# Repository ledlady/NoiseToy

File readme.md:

# NoiseToy
NoiseToy is a raspberry pi powered effect pedal.
Project files will follow soon.

This Project is inspired by and is based on the Pedal-Pi Project by Electrosmash: https://www.electrosmash.com/pedal-pi
Software followes mpi3d: https://github.com/mpi3d/pedal-pi

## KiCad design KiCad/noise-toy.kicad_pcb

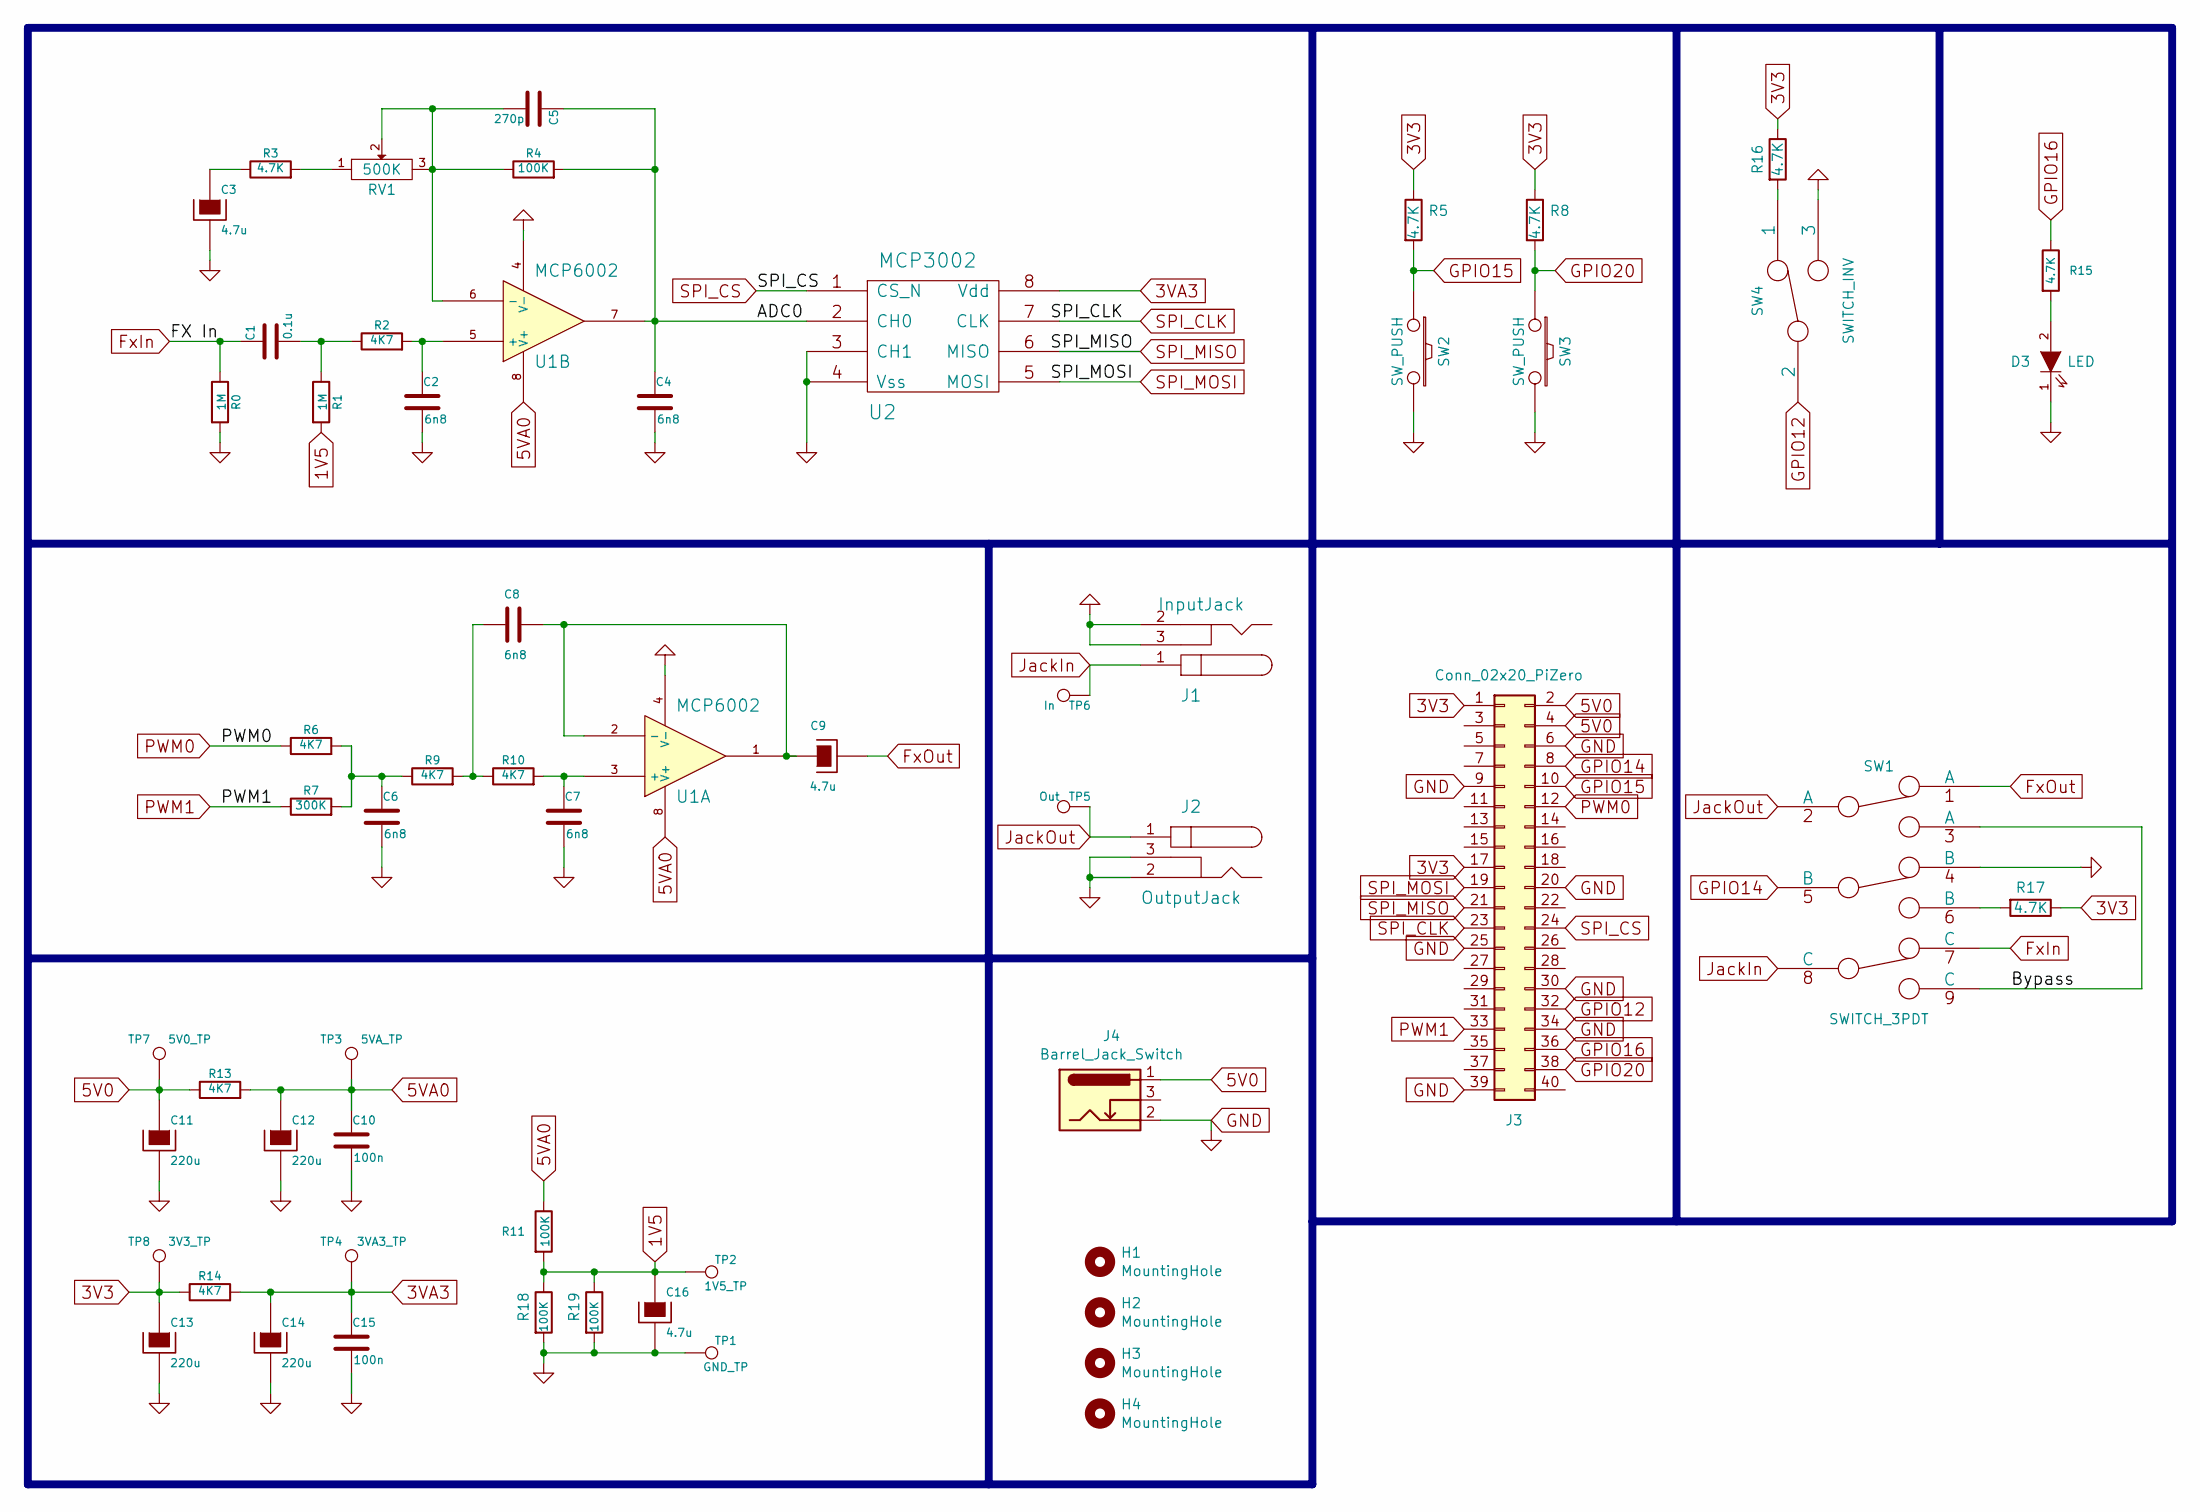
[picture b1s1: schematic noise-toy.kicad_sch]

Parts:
C1: 0.1u; C_Rect_L4.0mm_W2.5mm_P2.50mm
C2, C4, C6, C7, C8: 6n8; C_Rect_L4.0mm_W2.5mm_P2.50mm
C3, C9, C16: 4.7u; CP_Radial_D5.0mm_P2.00mm
C5: 270p; C_Rect_L4.0mm_W2.5mm_P2.50mm
C10, C15: 100n; C_Rect_L7.0mm_W2.5mm_P5.00mm
C11, C12, C13, C14: 220u; CP_Radial_D6.3mm_P2.50mm
D3: LED; LED_D5.0mm
H1, H2, H3, H4: MountingHole; MountingHole_3.2mm_M3
J1: InputJack; Audio_TRS_635_Stereo
J2: OutputJack; Audio_TRS_635_Stereo
J3: Conn_02x20_PiZero; PinHeader_2x20_P2.54mm_Vertical
J4: Barrel_Jack_Switch; BarrelJack_Horizontal
R0, R1: 1M; R_Axial_DIN0207_L6.3mm_D2.5mm_P10.16mm_Horizontal
R2, R6, R9, R10, R13, R14: 4K7; R_Axial_DIN0207_L6.3mm_D2.5mm_P10.16mm_Horizontal
R3, R5, R8, R15, R16, R17: 4.7K; R_Axial_DIN0207_L6.3mm_D2.5mm_P10.16mm_Horizontal
R4, R11, R18, R19: 100K; R_Axial_DIN0207_L6.3mm_D2.5mm_P10.16mm_Horizontal
R7: 300K; R_Axial_DIN0207_L6.3mm_D2.5mm_P10.16mm_Horizontal
RV1: 500K; Amphenol_N6S25T0C
SW1: SWITCH_3PDT; Switch_3PDT
SW2, SW3: SW_PUSH; Button_SPST
SW4: SWITCH_INV; Switch_SPDT
TP1: GND_TP; TestPoint_Pad_D2.5mm
TP2: 1V5_TP; TestPoint_Pad_D2.5mm
TP3: 5VA_TP; TestPoint_Pad_D2.5mm
TP4: 3VA3_TP; TestPoint_Pad_D2.5mm
TP5: Out; TestPoint_Pad_D2.5mm
TP6: In; TestPoint_Pad_D2.5mm
TP7: 5V0_TP; TestPoint_Pad_D2.5mm
TP8: 3V3_TP; TestPoint_Pad_D2.5mm
U1: MCP6002; DIP-8_W7.62mm_Socket_LongPads
U2: MCP3002; DIP-8_W7.62mm_Socket_LongPads

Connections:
1V5: C16.1, R1.2, R11.2, R18.1, R19.1, TP2.1
3V3: C13.1, J3.1, J3.17, R5.1, R8.1, R14.1, R16.1, R17.1, TP8.1
3VA3: C14.1, C15.1, R14.2, TP4.1, U2.8 (Vdd)
5V0: C11.1, J3.2, J3.4, J4.1, R13.1, TP7.1
5VA0: C10.1, C12.1, R11.1, R13.2, TP3.1, U1.8 (V+)
/ADC0: C4.1, C5.1, R4.2, U1.7, U2.2 (CH0)
/Bypass: SW1.3 (A), SW1.9 (C)
FxIn: C1.1, R0.1, SW1.7 (C)
FxOut: C9.2, SW1.1 (A)
GND: C2.2, C3.2, C4.2, C6.2, C7.2, C10.2, C11.2, C12.2, C13.2, C14.2, C15.2, C16.2, D3.1 (K), J1.2, J1.3, J2.2, J2.3, J3.6, J3.9, J3.20, J3.25, J3.30, J3.34, J3.39, J4.2, R0.2, R18.2, R19.2, SW1.4 (B), SW2.2, SW3.2, SW4.3, TP1.1, U1.4 (V-), U2.3 (CH1), U2.4 (Vss)
GPIO12: J3.32, SW4.2
GPIO14: J3.8, SW1.5 (B)
GPIO15: J3.10, R5.2, SW2.1
GPIO16: J3.36, R15.1
GPIO20: J3.38, R8.2, SW3.1
JackIn: J1.1, SW1.8 (C), TP6.1
JackOut: J2.1, SW1.2 (A), TP5.1
unnamed: C1.2, R1.1, R2.1
unnamed: C2.1, R2.2, U1.5 (+)
unnamed: C3.1, R3.1
unnamed: C5.2, R4.1, RV1.2, RV1.3, U1.6 (-)
unnamed: C6.1, R6.2, R7.2, R9.1
unnamed: C7.1, R10.2, U1.3 (+)
unnamed: C8.1, C9.1, U1.1, U1.2 (-)
unnamed: C8.2, R9.2, R10.1
unnamed: D3.2 (A), R15.2
unnamed: R3.2, RV1.1
unnamed: R16.2, SW4.1
unnamed: R17.2, SW1.6 (B)
PWM0: J3.12, R6.1
PWM1: J3.33, R7.1
SPI_CLK: J3.23, U2.7 (CLK)
SPI_CS: J3.24, U2.1 (CS_N)
SPI_MISO: J3.21, U2.6 (MISO)
SPI_MOSI: J3.19, U2.5 (MOSI)

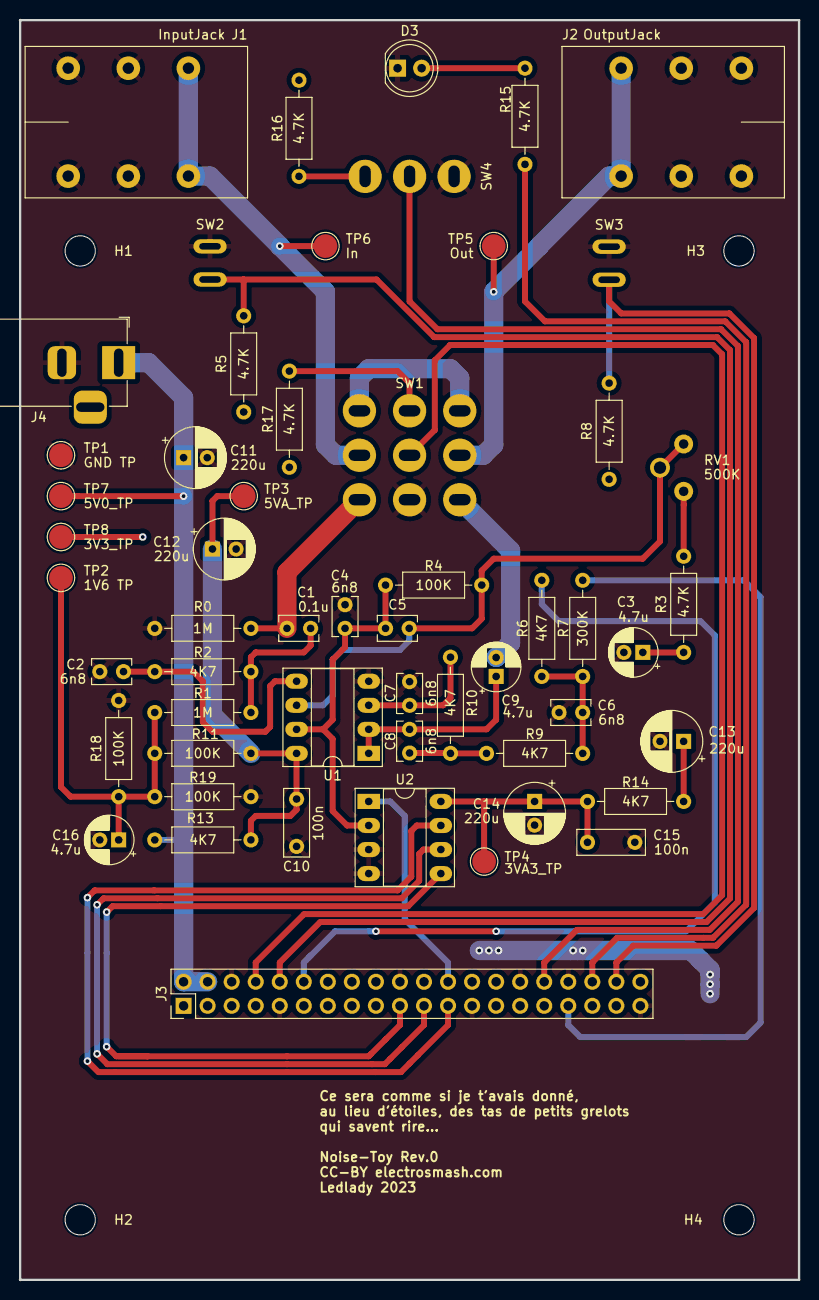
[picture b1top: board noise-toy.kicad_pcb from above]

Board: 2 copper layers, 82.3 x 133.1 mm, 59 parts (0 on the bottom side), 35 nets.

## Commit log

2023-09-11 Added KiCad7 design files
2023-09-11 Fixed wrong hole size in TRS jack Moved footprints to noise-toy.pretty
2023-09-11 Changed position of TRS jack
2023-09-11 Changed pcb attribution
2023-09-11 Added schematic and documentation notes
2023-09-11 Added jlcpcb gerber files to production folder
2023-09-11 Added attribution to pcb
2023-09-11 Added attribution to readme.md
2023-09-11 Added todo list to doku readme
2023-11-20 Added WIP library code

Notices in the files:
KiCad/noise-toy.kicad_pcb:
CC-BY electrosmash.com
